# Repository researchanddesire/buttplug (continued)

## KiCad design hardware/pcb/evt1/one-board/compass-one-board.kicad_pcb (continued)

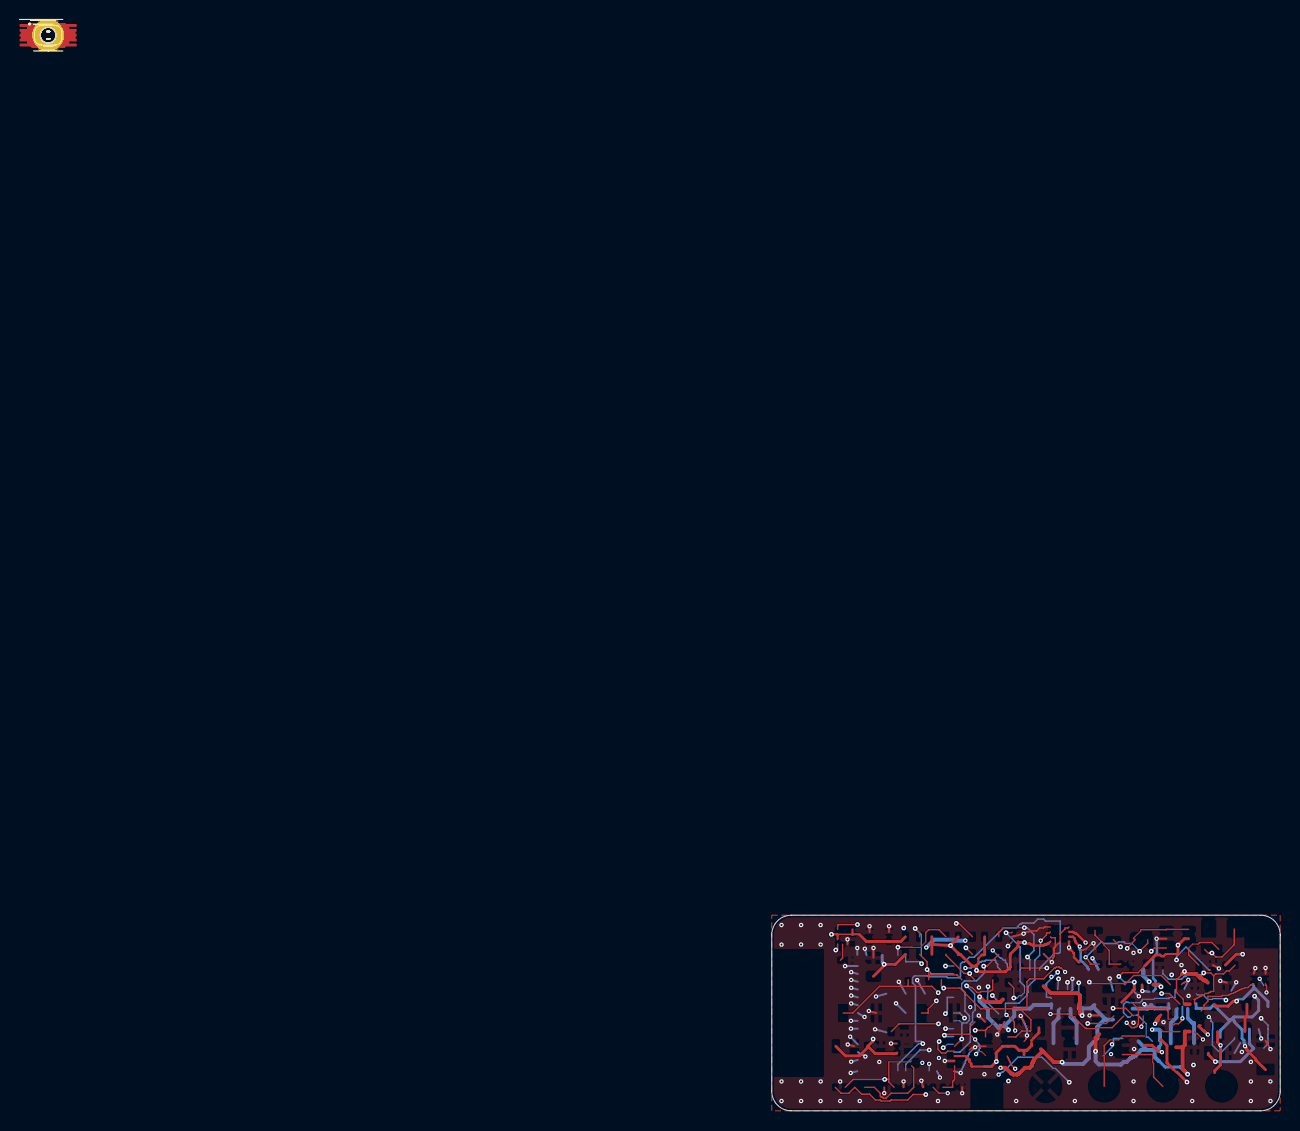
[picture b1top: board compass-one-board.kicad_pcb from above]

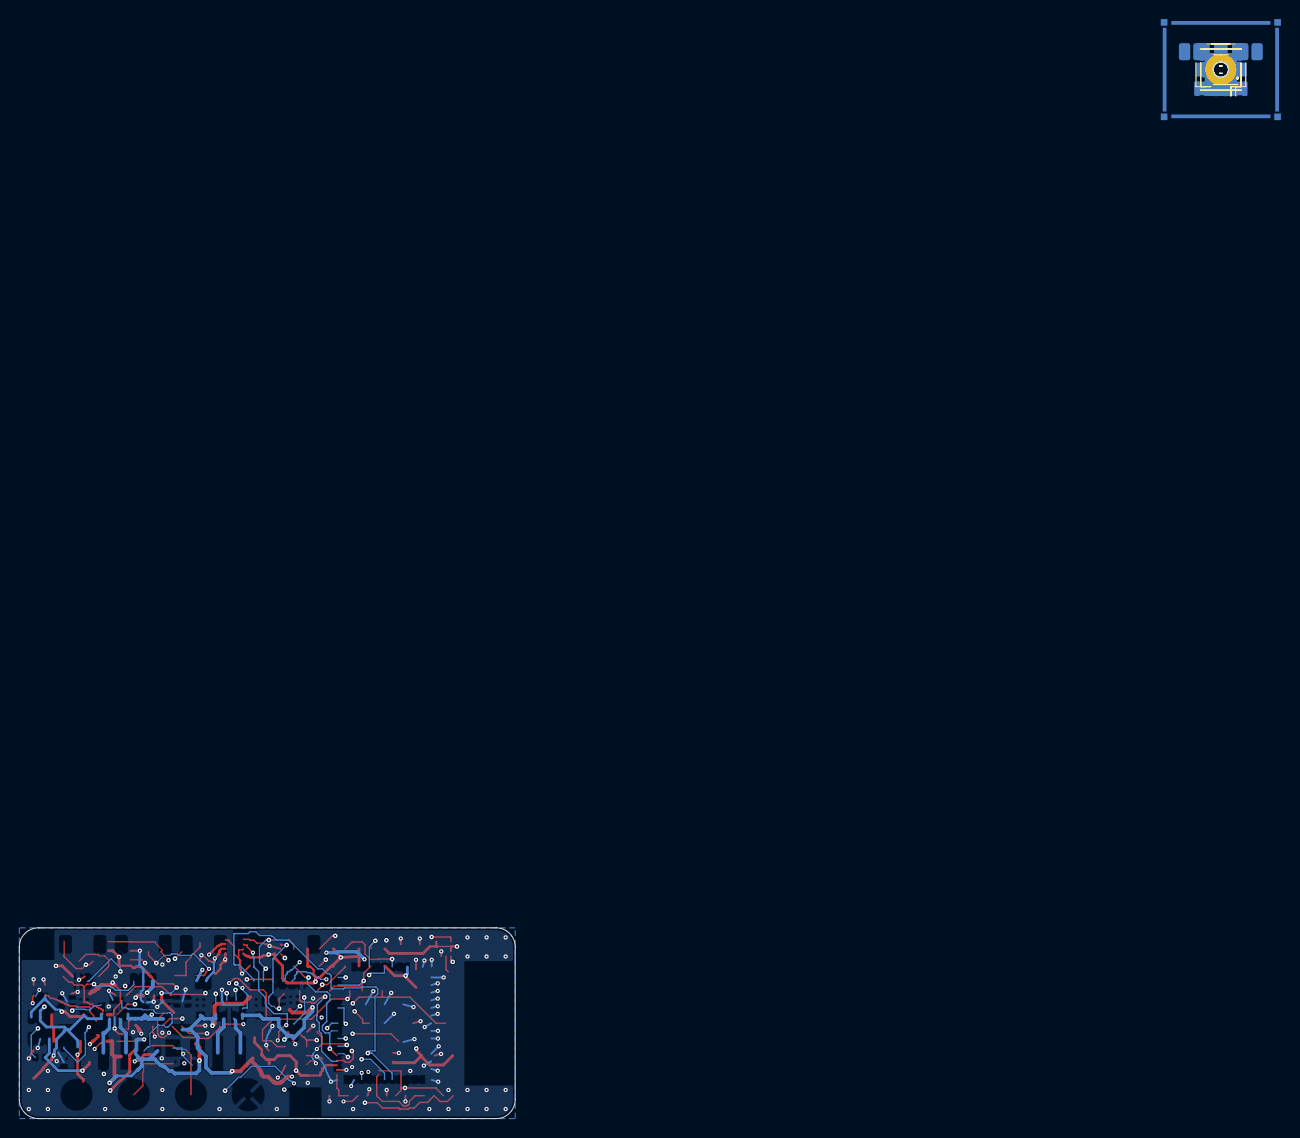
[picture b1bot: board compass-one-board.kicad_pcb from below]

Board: 4 copper layers, 52.0 x 20.0 mm, 109 parts (27 on the bottom side), 54 nets.

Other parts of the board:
MH1, MH3: PROVISIONAL M1.4 support

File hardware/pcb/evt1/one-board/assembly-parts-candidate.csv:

Comment,Designator,Footprint,Manufacturer Part Number,Baseline MPN
4.7uF 16V X7R,C1,Murata_GRM21_0805_Reflow,GRM21BR71C475KE51L,GRM21BR71A475KA73L
4.7uF 16V X7R,C2,Murata_GRM21_0805_Reflow,GRM21BR71C475KE51L,GRM21BR71A475KA73L
4.7uF 16V X7R,C3,Murata_GRM21_0805_Reflow,GRM21BR71C475KE51L,GRM21BR61A106KE19L
10uF 10V,C11,Murata_GRM21_0805_Reflow,GRM21BR61A106KE19L,GRM21BR61A106KE19L
22uF 10V X7R,C13,Murata_GRM31_1206_Reflow,GRM31CR71A226KE15L,GRM31CR71A226KE15L
22uF 10V X7R,C14,Murata_GRM31_1206_Reflow,GRM31CR71A226KE15L,GRM31CR71A226KE15L
22uF 10V X7R,C15,Murata_GRM31_1206_Reflow,GRM31CR71A226KE15L,GRM31CR71A226KE15L
100nF 10V,C16,Murata_GRM18_0603_Reflow,GRM188R71C104KA01D,GRM188R71C104KA01D
10uF 10V X5R 0603 HF,C51,TDK_C1608_0603_Reflow,CL10A106KP8NNNC,C1608X5R1A106K080AC
10uF 10V X5R 0603 HF,C52,TDK_C1608_0603_Reflow,CL10A106KP8NNNC,C1608X5R1A106K080AC
1.5uH / Isat>=4A candidate,L1,L_Coilcraft_XxL4020,XFL4020-152MEC,XFL4020-152MEC
8.87k 1% / ~100mA,R1,R_0402_1005Metric,TC0210B8871TCC,TNPW04028K87BEED
3.24k 1%,R2,R_0402_1005Metric,RT0402BRD073K24L,TNPW04023K24BEED
10k,R3,R_0402_1005Metric,TNPW040210K0BEED,TNPW040210K0BEED
10k,R4,R_0402_1005Metric,TNPW040210K0BEED,TNPW040210K0BEED
10k,R5,R_0402_1005Metric,TNPW040210K0BEED,TNPW040210K0BEED
312k 0.1%,R11,Vishay_TNPW0603_IEC_Reflow,RT0603BRD07312KL,TNPW0603312KBEEA
100k 0.1%,R12,Vishay_TNPW0603_IEC_Reflow,TNPW0603100KBEEA,TNPW0603100KBEEA
10k,R13,Vishay_TNPW0603_IEC_Reflow,TNPW060310K0BEEA,TNPW060310K0BEEA
BQ24074RGT candidate,U1,TI_RGT0016C_3x3mm_BQ24074_EP1.68mm,BQ24074RGTR,BQ24074RGTR
TPS63070RNM candidate,U2,TI_RNM0015A_2.5x3mm_TPS63070,TPS63070RNMR,TPS63070RNMR
10uF 10V,C31,Murata_GRM21_0805_Reflow,GRM21BR61A106KE19L,GRM21BR61A106KE19L
100nF,C32,Murata_GRM18_0603_Reflow,GRM188R71C104KA01D,GRM188R71C104KA01D
1uF,C33,TDK_C1608_0603_Reflow,CGA3E1X7R1V105KT000N,C1608X7R1E105K080AB
100nF,C34,Murata_GRM18_0603_Reflow,GRM188R71C104KA01D,GRM188R71C104KA01D
SERVICE_USB_BOOT,J4,JST_SH_SM06B-SRSS-TB_1x06-1MP_P1.00mm_Horizontal,SM06B-SRSS-TB(LF)(SN),SM06B-SRSS-TB(LF)(SN)
10k,R31,Vishay_TNPW0603_IEC_Reflow,TNPW060310K0BEEA,TNPW060310K0BEEA
10k,R32,Vishay_TNPW0603_IEC_Reflow,TNPW060310K0BEEA,TNPW060310K0BEEA
10k,R33,Vishay_TNPW0603_IEC_Reflow,TNPW060310K0BEEA,TNPW060310K0BEEA
10k,R34,Vishay_TNPW0603_IEC_Reflow,TNPW060310K0BEEA,TNPW060310K0BEEA
10k,R35,Vishay_TNPW0603_IEC_Reflow,TNPW060310K0BEEA,TNPW060310K0BEEA
10k,R36,Vishay_TNPW0603_IEC_Reflow,TNPW060310K0BEEA,TNPW060310K0BEEA
4.7k,R37,Vishay_TNPW0603_IEC_Reflow,TNPW06034K70BEEA,TNPW06034K70BEEA
4.7k,R38,Vishay_TNPW0603_IEC_Reflow,TNPW06034K70BEEA,TNPW06034K70BEEA
1.00M 1%,R39,Vishay_TNPW0805_IEC_Reflow,TNPW08051M00BEEA,TNPW08051M00BEEA
1.00M 1%,R40,Vishay_TNPW0805_IEC_Reflow,TNPW08051M00BEEA,TNPW08051M00BEEA
POWER / momentary,SW1,SW_SPST_B3U-1000P,B3U-1000P,B3U-1000P
MODE / momentary,SW2,SW_SPST_B3U-1000P,B3U-1000P,B3U-1000P
ESP32-C3-MINI-1-H4X,U6,Espressif_ESP32-C3-MINI-1_53Pads,ESP32-C3-MINI-1-H4X,ESP32-C3-MINI-1-N4X
100nF,C43,Murata_GRM18_0603_Reflow,GRM188R71C104KA01D,GRM188R71C104KA01D
100nF,C44,Murata_GRM18_0603_Reflow,GRM188R71C104KA01D,GRM188R71C104KA01D
AO3400A,Q1,SOT-23,AO3400A,AO3400A
10.0k 0.1%,R42,R_0402_1005Metric,TNPW040210K0BEED,TNPW040210K0BEED
715k 0.1%,R43,RESI_PTFR0805_C16003,PTFR0805B715KP9,TNPW0805715KBEEA
110k 0.1%,R44,Vishay_TNPW0603_IEC_Reflow,TNPW0603110KBEEA,TNPW0603110KBEEA
200k 0.1%,R45,Vishay_TNPW0603_IEC_Reflow,ERA3AEB204V,TNPW0603200KBEEA
11k 1%,R46,R_0402_1005Metric,RT0402BRD0711KL,TNPW040211K0BEED
1k 1%,R47,R_0402_1005Metric,TNPW04021K00BEED,TNPW04021K00BEED
100k 1%,R48,R_0402_1005Metric,TNPW0402100KBEED,TNPW0402100KBEED
TPS3700DDCR,U8,TSOT-23-6,TPS3700DDCR,TPS3700DDCR
TPS3808G33QDBVRQ1,U9,SOT-23-6,TPS3808G33QDBVRQ1,TPS3808G33DBVR
100nF,C71,C_0402_1005Metric,GRM155R71C104KA88D,GRM155R71C104KA88D
BAT54WS-E3-08,D71,D_SOD-323,BAT54WS-E3-08,BAT54WS-E3-08
BAT54WS-E3-08,D72,D_SOD-323,BAT54WS-E3-08,BAT54WS-E3-08
BAT54WS-E3-08,D73,D_SOD-323,BAT54WS-E3-08,BAT54WS-E3-08
10k,R71,R_0402_1005Metric,TNPW040210K0BEED,TNPW040210K0BEED
TPS3422EGDRYR,U71,Texas_USON-6_1x1.45mm_P0.5mm_SMD,TPS3422EGDRYR,TPS3422EGDRYR
10uF 10V,C21,Murata_GRM21_0805_Reflow,GRM21BR61A106KE19L,GRM21BR61A106KE19L
22uF 10V X7R,C23,Murata_GRM31_1206_Reflow,GRM31CR71A226KE15L,GRM31CR71A226KE15L
22uF 10V X7R,C24,Murata_GRM31_1206_Reflow,GRM31CR71A226KE15L,GRM31CR71A226KE15L
22uF 10V X7R,C25,Murata_GRM31_1206_Reflow,GRM31CR71A226KE15L,GRM31CR71A226KE15L
100nF 10V,C26,Murata_GRM18_0603_Reflow,GRM188R71C104KA01D,GRM188R71C104KA01D
100nF,C27,Murata_GRM18_0603_Reflow,GRM188R71C104KA01D,GRM188R71C104KA01D
100nF,C28,C_0402_1005Metric,GRM155R71C104KA88D,GRM155R71C104KA88D
100nF,C29,C_0402_1005Metric,GRM155R71C104KA88D,GRM155R71C104KA88D
47uF 10V,C30,Murata_GRM32_1210_Reflow,GRM32ER61A476KE20L,GRM32ER61A476KE20L
10uF 10V X5R 0603 HF,C53,TDK_C1608_0603_Reflow,CL10A106KP8NNNC,C1608X5R1A106K080AC
10uF 10V X5R 0603 HF,C54,TDK_C1608_0603_Reflow,CL10A106KP8NNNC,C1608X5R1A106K080AC
MOTOR_2PIN,J3,JST_SH_SM02B-SRSS-TB_1x02-1MP_P1.00mm_Horizontal,SM02B-SRSS-TB(LF)(SN),SM02B-SRSS-TB(LF)(SN)
1.5uH / Isat>=4A candidate,L2,L_Coilcraft_XxL4020,XFL4020-152MEC,XFL4020-152MEC
360k 0.1%,R21,RESI_PTFR0805_C16003,PTFR0805B360KN9,TNPW0805362KBEEA
100k 0.1%,R22,Vishay_TNPW0603_IEC_Reflow,TNPW0603100KBEEA,TNPW0603100KBEEA
100k,R23,R_0402_1005Metric,TNPW0402100KBEED,TNPW0402100KBEED
100k,R24,R_0402_1005Metric,TNPW0402100KBEED,TNPW0402100KBEED
100k,R25,R_0402_1005Metric,TNPW0402100KBEED,TNPW0402100KBEED
10k,R26,Vishay_TNPW0603_IEC_Reflow,TNPW060310K0BEEA,TNPW060310K0BEEA
TPS63070RNM candidate,U3,TI_RNM0015A_2.5x3mm_TPS63070,TPS63070RNMR,TPS63070RNMR
SN74LVC1G11DBV candidate,U4,SOT-23-6,SN74LVC1G11DBVR,SN74LVC1G11DBVR
DRV8212DSG candidate,U5,WSON-8-1EP_2x2mm_P0.5mm_EP0.9x1.6mm,DRV8212DSGR,DRV8212DSGR
100nF,C61,C_0402_1005Metric,GRM155R71C104KA88D,GRM155R71C104KA88D
10nF,C62,C_0402_1005Metric,GRM155R71H103KA88D,GRM155R71H103KA88D
10nF,C63,C_0402_1005Metric,GRM155R71H103KA88D,GRM155R71H103KA88D
10nF 50V X7R,C88,C_0402_1005Metric,GRM155R71H103KA88D,
TIP NTC / GND,J5,JST_SH_BM02B-SRSS-TB_1x02-1MP_P1.00mm_Vertical,BM02B-SRSS-TB(LF)(SN),BM02B-SRSS-TB(LF)(SN)
PACK MONITOR NTC / GND,J8,JST_SH_SM02B-SRSS-TB_1x02-1MP_P1.00mm_Horizontal,SM02B-SRSS-TB(LF)(SN),
10k 0.1%,R61,R_0402_1005Metric,TNPW040210K0BEED,TNPW040210K0BEED
10k 0.1%,R62,R_0402_1005Metric,TNPW040210K0BEED,TNPW040210K0BEED
10k 0.1%,R63,R_0402_1005Metric,TNPW040210K0BEED,TNPW040210K0BEED
10k 0.1%,R88,R_0402_1005Metric,TNPW040210K0BEED,
ADS1115IDGSR /0x48,U7,VSSOP-10_3x3mm_P0.5mm,ADS1115IDGSR,ADS1115IDGSR
Schottky 1A/20V candidate,D1,Diodes_B140HW_SOD123_A1_K2,B140HW-7,B140HW-7
PTC 500mA candidate,F1,Fuse_1206_3216Metric,1206L050YR,1206L050YR
22R,R75,R_0402_1005Metric,RC0402FR-0722RL,TNPW040222R0BEED
22R,R76,R_0402_1005Metric,RC0402FR-0722RL,TNPW040222R0BEED
USBLC6-2SC6,U75,SOT-23-6,USBLC6-2SC6,USBLC6-2SC6
220nF,C81,C_0402_1005Metric,GRM155R71C224KA12D,GRM155R71C224KA12D
100nF,C82,C_0402_1005Metric,GRM155R71C104KA88D,GRM155R71C104KA88D
47uF 10V / Ceff>=10uF at3V3,C83,C_0805_2012Metric,MSASL21GBB5476MTNA01,C2012X5R1E226M125AC
100nF / VDDIO local,C84,C_0402_1005Metric,GRM155R71C104KA88D,GRM155R71C104KA88D
LSM303AGRTR,U81,LGA-12_2x2mm_P0.5mm,LSM303AGRTR,LSM303AGRTR
